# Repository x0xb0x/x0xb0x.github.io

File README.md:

# x0xb0x.github.io
Please view on [http://x0xb0x.github.io](http://x0xb0x.github.io)

All info licensed CC-BY, all software licenced MIT.

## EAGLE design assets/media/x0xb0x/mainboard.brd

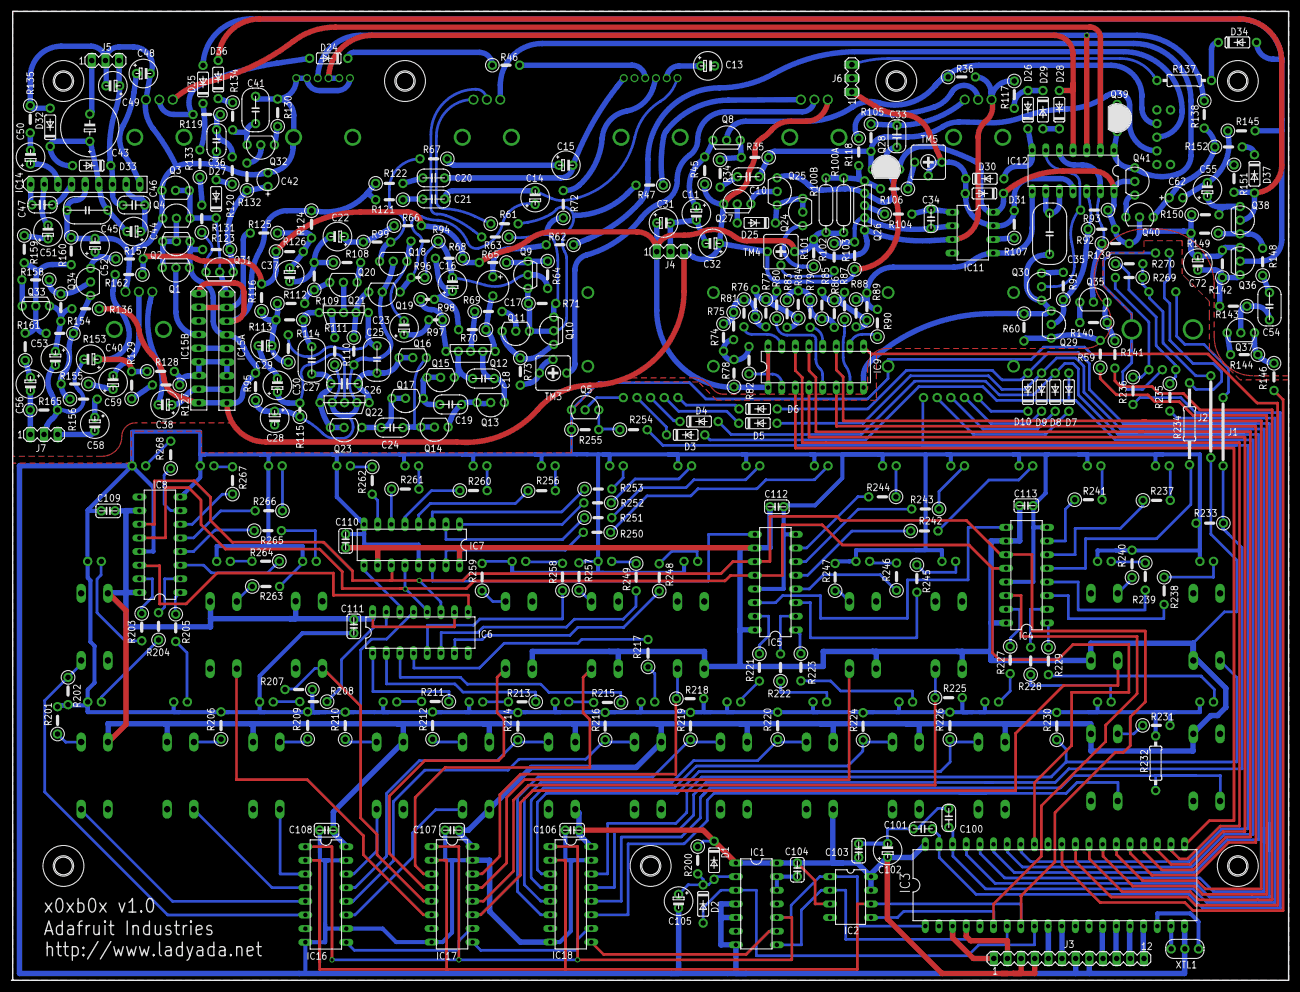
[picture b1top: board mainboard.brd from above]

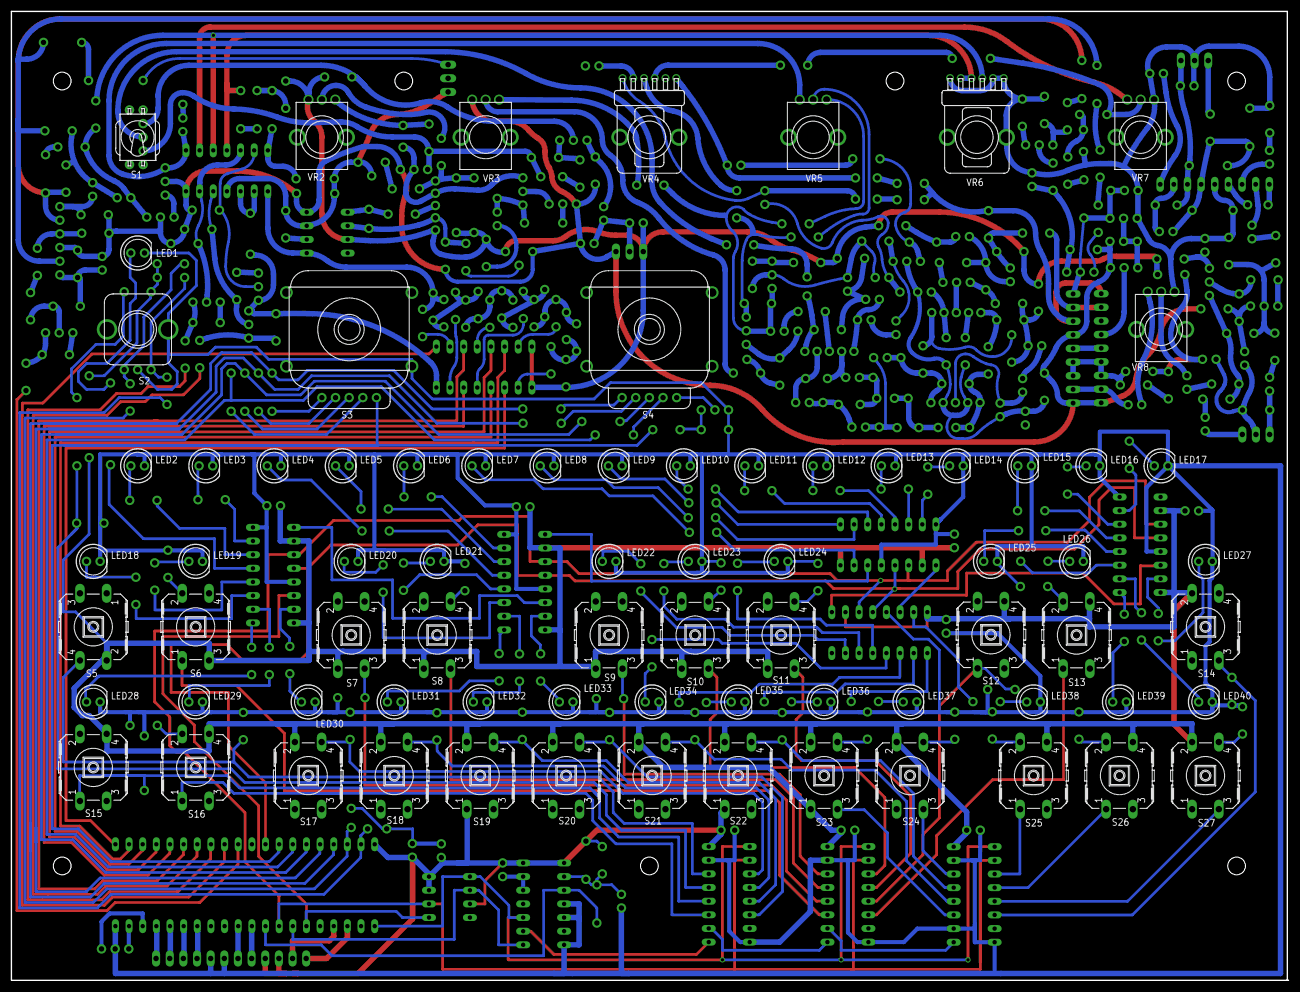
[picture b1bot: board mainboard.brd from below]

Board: 2 copper layers, 237.5 x 180.3 mm, 417 parts (74 on the bottom side), 324 nets.

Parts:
C10, C20, C21, C33, C46: .01; C050-024X044
C11, C13, C14, C15, C22, C23, C29, C38, C56, C58, C59, C105: 1/50; E5-6
C16, C30, C31, C32, C37, C40, C50, C52, C72: 10/16; E5-6
C17: 1/50; E3,5-8
C18: .018; C050-025X075
C19, C24, C36: .033; C050-025X075
C25, C27, C41: .1; C050-030X075
C26: .033; C075-032X103
C28, C44, C53, C55: 47/16; E5-6
C34, C100, C101: .001; C050-035X075
C35: .22; C050-045X075
C42, C62: 1/35; E2,5-7
C43: 1000/6.3; E5-5
C45: .068; C050-050X075
C47: .0068; C050-075X075
C48, C49: 100/6.3; E5-6
C51: 2.2/50; E5-6
C54: .047; C050-055X075
C102: 100/10; E5-6
C103, C104, C106, C107, C108, C109, C110, C111, C112, C113: .1; C050H075X075
D1, D2, D3, D4, D5, D6, D7, D8, D9, D10, D24, D25, D26, D27, D28, D29, D30, D31, D32, D33, D34, D35, D36, D37: 1N4148; DO35-10
IC1: 74126N; DIL14
IC2: AT25P; DIL08
IC3: MEGA162P; DIL40
IC4, IC5, IC6, IC7, IC8: 74HC595N; DIL16
IC9: 4174P; DIL16
IC11: DIL08
IC12: 4066N; DIL14
IC14: LA44140; SIP9
IC15A: SIP9
IC15B: BA6110; SIP9
IC16, IC17, IC18: 74HC165N; DIL16
J1: J12MM; 12
J2: J15MM; 15
J3: MA12-1
J4, J5, J6, J7: MA03-1
LED1, LED2, LED3, LED4, LED5, LED6, LED7, LED8, LED9, LED10, LED11, LED12, LED13, LED14, LED15, LED16, LED17, LED18, LED19, LED20, LED21, LED22, LED23, LED24, LED25, LED26, LED27, LED28, LED29, LED30, LED31, LED32, LED33, LED34, LED35, LED36, LED37, LED38, LED39, LED40: LED5MM
Q1, Q2, Q8, Q9, Q10, Q27, Q31, Q33, Q36, Q38: 2SA733P; TO92
Q3, Q4, Q5, Q11, Q13, Q14, Q15, Q16, Q18, Q20, Q24, Q25, Q29, Q30, Q32, Q34, Q35, Q37, Q40, Q41: 2SC536F
Q12, Q21, Q26: 2SC1583; SSIP5
Q17, Q23: 2SC536F; 2SC536_UNEVEN
Q19: 2SC536FUNEVEN; 2SC536_UNEVEN
Q22: 2SC2291; SSIP5
Q28, Q39: 2SK30
R34, R36, R47, R61, R64, R65, R94, R101, R105, R109, R112, R116, R142, R143, R144, R145, R148, R149, R201, R202, R203, R204, R205, R206, R207, R208, R209, R210, R211, R212, R213, R214, R215, R216, R217, R218, R219, R220, R221, R222, R223, R224, R225, R226, R227, R228, R229, R230, R231, R233, R237, R238, R239, R240, R241, R242, R243, R244, R245, R246, R247, R248, R249, R250, R251, R252, R253, R254, R255, R256, R257, R258, R259, R260, R261, R262, R263, R264, R265, R266, R267, R268, R269, R270: 10K; 0207/5V
R35, R59, R66, R72, R73, R92, R93, R99, R102, R113, R114, R118, R122, R139, R140, R141, R154, R156, R165: 100K; 0207/5V
R45, R60, R110, R111, R117, R129, R134, R146, R151: 22K; 0207/5V
R46, R119, R127, R155: 47K; 0207/5V
R62, R63, R121, R128, R131: 220K; 0207/5V
R67, R68, R69, R70, R71, R104, R107, R108, R124, R125, R126, R133, R162: 2.2K; 0207/5V
R74, R75, R76, R77, R78, R79, R80, R81, R82, R83, R84, R85, R86, R87, R88, R89: 200K; 0207/5V
R90: 200k; 0207/5V
R91, R200: 1M; 0207/5V
R95, R130, R132, R136, R152: 100; 0207/5V
R96, R97, R115: 10K; 0207/2V
R98: 2.2K; 0207/2V
R100A, R100B: THERMISTOR-7,5; R-7,5
R103, R235, R236: 220k; 0207/5V
R106: 27K; 0207/5V
R120: 22k; 0207/5V
R123: 1.5M; 0207/5V
R135: 4.7k; 0207/5V
R137: 1K; 0207/10
R138: 68K; 0207/5V
R150: 22; 0207/5V
R153: 100k; 0207/5V
R157, R158, R160: 10k; 0207/5V
R159: 33K; 0207/5V
R161: 1K; 0207/5V
R232: 10K; 0207/10
R234: 10K; 0207/15
S1: SWITCH_GND; NKKTOGGLE
S2: PEC11-S
S3, S4: GH3074
S5, S6, S7, S8, S9, S10, S11, S12, S13, S14, S15, S16, S17, S18, S19, S20, S21, S22, S23, S24, S25, S26, S27: B3F-40XX
TM3: 500K(B); 306
TM4: 50K(B); 306
TM5: 5K(B); 306
U$2, U$23, U$24, U$25, U$27, U$28, U$29: 1,3
VR2, VR7: 50K(B); EVU
VR3, VR5, VR8: 50K(A); EVU
VR4: 50K(B); ALPHADUAL
VR6: 1M(A); ALPHADUAL
XTL1: 2SC2021R; 2SC2021

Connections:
+5.333V: C31.+, IC9.1, IC9.16, IC11.3, J4.1, Q26.1, R36.2, R65.2, R66.2, R68.1, R78.1, R100A.2, R100B.1, R101.2, R116.2, R117.1, R126.1, R157.2, R162.1, TM4.3, VR2.3
+5V: C102.+, C103.1, C104.2, C106.2, C107.2, C108.2, C109.2, C110.2, C111.2, C112.2, C113.2, D1.C, IC1.1, IC1.14, IC2.3, IC2.7, IC2.8, IC3.40, IC4.10, IC4.16, IC5.10, IC5.16, IC6.10, IC6.16, IC7.10, IC7.16, IC8.10, IC8.16, IC16.16, IC17.16, IC18.16, J2.2, J3.3, J3.4, R200.1, S5.2, S6.3, S7.1, S8.1, S9.1, S10.1, S11.1, S12.4, S13.4, S14.2, S15.4, S16.4, S17.2, S18.2, S19.1, S19.2, S20.2, S21.2, S22.1, S22.2, S23.1, S23.2, S24.2, S25.4, S26.4, S27.2
+6V: C46.1, C49.+, D33.C, IC14.7, J5.3
+12V: C32.+, C72.+, D31.C, IC11.8, IC12.14, IC15A.4, IC15A.9, IC15B.9, J4.3, Q1.3, Q2.3, Q27.3, Q28.1, Q36.3, Q40.2, Q41.2, R45.1, R92.2, R93.1, R95.2, R103.1, R123.2, R136.1, R139.2, R142.2, R149.2, R150.1, TM4.1, VR3.3
ACCENT: IC3.28, R141.2
C48: C48.+, IC14.9
DINSYNC1: IC3.17, J3.12
DINSYNC2: IC3.16, J3.11
DINSYNC3: IC3.15, J3.10
DINSYNC4: IC3.14, J3.9
GATE: IC3.30, R146.2
GND: C11.-, C13.-, C16.-, C22.-, C28.-, C29.-, C30.-, C31.-, C32.-, C33.2, C35.2, C36.2, C37.-, C40.-, C41.2, C42.-, C45.2, C48.-, C49.-, C52.-, C53.-, C55.-, C62.-, C100.1, C101.1, C102.-, C103.2, C104.1, C105.-, C106.1, C107.1, C108.1, C109.1, C110.1, C111.1, C112.1, C113.1, D26.C, D30.A, D32.A, IC1.4, IC1.5, IC1.7, IC1.12, IC1.13, IC2.4, IC3.20, IC4.8, IC4.13, IC5.8, IC5.13, IC6.8, IC6.13, IC7.8, IC7.13, IC8.8, IC8.13, IC9.8, IC11.4, IC12.7, IC14.5, IC15A.5, IC15B.3, IC15B.5, IC16.8, IC16.10, IC16.15, IC17.8, IC17.15, IC18.8, IC18.15, J3.7, J3.8, J4.2, J5.2, J6.2, J7.2, LED1.K, LED2.K, LED3.K, LED4.K, LED5.K, LED6.K, LED7.K, LED8.K, LED9.K, LED10.K, LED11.K, LED12.K, LED13.K, LED14.K, LED15.K, LED16.K, LED17.K, LED18.K, LED19.K, LED20.K, LED21.K, LED22.K, LED23.K, LED24.K, LED25.K, LED26.K, LED27.K, LED28.K, LED29.K, LED30.K, LED31.K, LED32.K, LED33.K, LED34.K, LED35.K, LED36.K, LED37.K, LED38.K, LED39.K, LED40.K, Q3.3, Q4.3, Q5.3, Q9.2, Q29.3, Q30.3, Q35.3, Q37.3, Q39.2, Q39.3, R60.1, R64.2, R94.1, R96.1, R105.1, R108.1, R109.2, R130.2, R135.1, R140.2, R144.2, R145.1, R151.1, R160.1, R165.2, R201.2, R202.2, R206.2, R207.1, R209.2, R210.2, R212.2, R214.2, R216.2, R218.2, R219.2, R220.2, R224.2, R225.2, R226.2, R230.2, R231.2, R232.2, R233.2, R240.2, R247.2, R255.1, R257.2, R259.2, R263.2, S1.M1, S1.M2, S1.M3, S1.M4, S2.C, S2.P$1, S2.P$2, S3.MT1, S3.MT2, S3.MT3, S3.MT4, S4.MT1, S4.MT2, S4.MT3, S4.MT4, VR2.1, VR2.M1, VR2.M2, VR3.M1, VR3.M2, VR4.1A, VR4.M1, VR4.M2, VR5.M1, VR5.M2, VR6.1A, VR6.2A, VR6.3A, VR6.M1, VR6.M2, VR7.1, VR7.M1, VR7.M2, VR8.1, VR8.M1, VR8.M2, XTL1.2
LED_LATCH: IC3.32, IC4.12, IC5.12, IC6.12, IC7.12, IC8.12
MIDI_IN: IC3.10, J3.5
MIDI_OUT: IC3.11, J3.6
unnamed: C51.-, IC14.2
unnamed: C51.+, R159.1
unnamed: C50.+, IC14.3
unnamed: C50.-, R135.2
unnamed: Q34.3, R153.1, R155.2, R156.1
unnamed: C56.+, R161.1
unnamed: C56.-, J7.1, R165.1
unnamed: C47.1, IC14.4
unnamed: C47.2, IC14.1
unnamed: C43.-, J5.1
unnamed: C43.+, C44.-, C45.1, D32.C, D33.A, IC14.6
unnamed: Q33.2, R153.2, R159.2, R160.2, R161.2
unnamed: C44.+, C46.2, IC14.8
unnamed: Q34.2, R154.1, R158.1
unnamed: Q33.1, R158.2
unnamed: C53.+, Q33.3, R136.2, R154.2
unnamed: C52.+, Q34.1, R157.1
unnamed: C59.+, R155.1
unnamed: C58.+, R156.2
unnamed: C58.-, J7.3
unnamed: C20.1, R122.2
unnamed: C37.+, R124.2, R125.1, R126.2
unnamed: IC7.1, R252.2
unnamed: IC15A.2, IC15B.2, R125.2
unnamed: C21.1, R121.1
unnamed: C15.-, C20.2, VR4.2A
unnamed: C14.-, C21.2, VR4.3A
unnamed: IC15A.6, IC15A.7, IC15B.6, IC15B.7, R127.1, R128.2
unnamed: IC15B.4, Q1.2
unnamed: R127.2, R129.1
unnamed: C40.+, R128.1, R129.2, R162.2
unnamed: C38.-, VR8.3
unnamed: D27.A, R120.1
unnamed: C36.1, R119.1, R120.2
unnamed: D24.A, R119.2, VR7.2
unnamed: C55.+, Q38.3, R150.2
unnamed: C72.-, Q36.1, R142.1, R143.2
unnamed: D34.A, D35.A, Q36.2, R145.2
unnamed: Q38.1, R148.2, R149.1
unnamed: D37.C, R152.2
unnamed: C54.1, R148.1
unnamed: C54.2, Q37.2, R143.1
unnamed: Q37.1, R144.1, R146.1
unnamed: D36.A, D37.A, Q38.2, R151.2
unnamed: C62.+, Q40.1, R138.2, R152.1
unnamed: Q40.3, Q41.1
unnamed: C38.+, IC15A.8, IC15B.8
unnamed: R61.1, VR5.1
unnamed: D26.A, D29.C, R117.2
unnamed: D28.C, D29.A
unnamed: D28.A, IC12.4, VR6.2B, VR6.3B
unnamed: IC12.1, Q39.1, Q41.3, VR5.3
unnamed: Q35.1, R140.1, R141.1
unnamed: Q32.3, R130.1
unnamed: IC12.5, IC12.13, Q35.2, R139.1
unnamed: D34.C, R137.1
unnamed: Q5.1, R254.1, R255.2
unnamed: Q12.5, R97.1, R98.1
unnamed: D35.C, R133.2
unnamed: D36.C, R134.1
unnamed: C41.1, Q32.1, R134.2
unnamed: Q32.2, R132.2
unnamed: C42.+, Q31.1, R123.1, R132.1
unnamed: D27.C, IC15A.1, Q3.1, Q3.2, Q4.1, Q31.2
unnamed: Q31.3, R131.1
unnamed: R131.2, R133.1
unnamed: IC9.10, R90.1
unnamed: R236.1, R269.2, S2.B
unnamed: IC4.7, R241.1
unnamed: C35.1, IC12.9, IC12.10
unnamed: IC12.6, Q30.2, R93.2
unnamed: Q30.1, R91.2
unnamed: IC11.6, R107.1
unnamed: R85.2, R86.1, R87.2, R88.2, R89.1
unnamed: IC1.9, IC18.9
unnamed: IC12.12, Q29.2, R91.1, R92.1
unnamed: R79.1, R83.1, R84.2, R85.1, R86.2
unnamed: C105.+, D1.A, D2.C, IC1.2, R200.2
unnamed: IC9.15, R81.2
unnamed: IC9.2, R82.1
unnamed: IC9.12, R79.2
unnamed: Q29.1, R59.2, R60.2
unnamed: C34.1, IC11.1, R104.2
unnamed: C34.2, IC11.2, Q26.2, R102.1, R103.2
unnamed: Q26.5, R100A.1, R100B.2, R106.2, R118.2
unnamed: IC4.6, R237.1
unnamed: Q26.3, R104.1
unnamed: R118.1, VR2.2
unnamed: D25.A, Q27.2
unnamed: D25.C, Q24.1, Q24.2, Q25.1
unnamed: Q24.3, R101.1
unnamed: Q25.2, Q27.1
unnamed: IC17.5, R207.2, S12.1
unnamed: C10.1, Q28.3, R35.1, R105.2, S1.1
unnamed: Q8.1, R34.1, R35.2
unnamed: C10.2, R34.2
unnamed: IC11.5, IC12.8, R88.1, R89.2, R90.2
unnamed: C33.1, Q25.3, Q26.4, Q28.2
unnamed: R102.2, TM4.2
unnamed: C30.+, Q22.3, R115.2
unnamed: C24.1, Q14.1, Q14.2, Q16.3
unnamed: C19.1, Q13.1, Q13.2, Q14.3
unnamed: C18.2, Q12.2, Q13.3
unnamed: C24.2, Q17.1, Q17.2, Q23.3
unnamed: C26.2, C27.1, Q22.5, Q23.1, Q23.2
unnamed: C18.1, Q12.4, Q15.3
unnamed: C28.+, Q18.2, Q19.2, Q22.2, Q22.4, R95.1, R110.2, R111.1, R115.1
unnamed: C17.+, R62.2
unnamed: C17.-, Q12.1, R70.1
unnamed: C16.+, R68.2, R70.2, R98.2
unnamed: R62.1, S1.2
unnamed: Q12.3, R69.1
unnamed: C23.+, R97.2
unnamed: LED6.A, R244.1
unnamed: C23.-, Q18.3, R94.2
unnamed: Q18.1, R67.2, R99.2
unnamed: C22.+, R66.1, R99.1
unnamed: C15.+, R67.1
unnamed: Q10.1, R63.1, R71.2, R72.1
unnamed: Q20.1, R109.1, R112.2
unnamed: Q20.3, R108.2
unnamed: LED7.A, R250.1
unnamed: C25.2, Q21.1, R114.2
unnamed: Q20.2, Q21.3
unnamed: Q19.1, Q21.2, R110.1
unnamed: C27.2, Q21.5, R113.1
unnamed: R47.1, VR3.1
unnamed: C25.1, C26.1, Q16.1, Q16.2, Q22.1
unnamed: C14.+, Q19.3, R96.2
unnamed: Q11.2, R69.2
unnamed: Q10.3, Q11.1, R73.1
unnamed: Q21.4, R111.2
unnamed: Q9.1, R64.1, R65.1
unnamed: IC12.2, VR7.3
unnamed: R73.2, TM3.2, TM3.3
unnamed: R72.2, VR4.2B
unnamed: R63.2, VR5.2
unnamed: TM3.1, VR3.2
unnamed: R76.2, R77.1, R80.2, R83.2, R84.1
unnamed: IC12.3, R138.1, VR6.1B
unnamed: R106.1, TM5.1
unnamed: C59.-, VR8.2
unnamed: D24.C, R46.1
unnamed: R46.2, VR4.1B
unnamed: C13.+, VR4.3B
unnamed: R257.1, S10.4
unnamed: IC17.14, R218.1, S9.3
unnamed: IC17.13, S8.3
unnamed: IC17.12, R225.1, S7.3
unnamed: R259.1, S11.4
unnamed: IC18.14, R230.1, S5.4
unnamed: D3.C, S4.P$1
unnamed: IC18.12, R232.1, S15.1
unnamed: R206.1, S26.2
unnamed: IC16.5, S27.3
unnamed: IC17.9, IC18.10
unnamed: IC18.4, R224.1, S18.4
unnamed: IC17.4, S11.3
unnamed: D4.C, S4.P$2
unnamed: R209.1, S25.2
unnamed: IC4.5, R234.1
unnamed: IC5.9, IC7.14
unnamed: IC5.6, R243.2
unnamed: IC5.7, R244.2
unnamed: IC5.5, R242.1
unnamed: IC7.15, R250.2
unnamed: IC7.2, R251.1
unnamed: LED1.A, R234.2
unnamed: LED2.A, R237.2
unnamed: IC7.3, R253.1
unnamed: IC7.4, R256.1
unnamed: LED14.A, R262.1
unnamed: IC8.3, R264.1
unnamed: IC8.6, R267.1
unnamed: IC8.7, R268.1
unnamed: IC8.5, R266.2
unnamed: IC5.1, R223.1
unnamed: IC8.4, R265.1
unnamed: IC5.2, R222.2
unnamed: IC5.15, R221.1
unnamed: IC5.4, R246.1
unnamed: IC5.3, R245.2
unnamed: IC4.3, R238.2
unnamed: IC4.4, R239.2
unnamed: IC4.1, R229.1
unnamed: IC7.6, R261.1
unnamed: IC7.7, R262.2
unnamed: IC7.5, R260.1
unnamed: IC4.2, R228.2
unnamed: IC4.15, R227.1
unnamed: IC8.15, R203.1
unnamed: IC8.1, R205.1
unnamed: IC8.2, R204.2
unnamed: IC6.15, R208.1
unnamed: IC6.1, R211.1
unnamed: IC6.2, R213.1
unnamed: IC6.3, R215.1
unnamed: IC6.4, R217.2
unnamed: IC6.7, R248.1
unnamed: IC6.6, R249.2
unnamed: IC6.5, R258.1
unnamed: IC16.9, IC17.10
unnamed: IC16.13, R214.1, S22.4
unnamed: R210.1, S24.4
unnamed: IC16.11, S23.3
unnamed: IC16.4, S26.1
unnamed: IC18.6, R219.1, S20.4
unnamed: IC16.12, R216.1, S21.4
unnamed: R240.1, S6.2
unnamed: IC16.14, S24.3
unnamed: IC9.7, R87.1
unnamed: R201.1, S27.4
unnamed: R235.1, R270.1, S2.A
unnamed: R212.1, S23.4
unnamed: IC9.5, R80.1
unnamed: R74.2, R75.2, R78.2, R82.2
unnamed: LED9.A, R252.1
unnamed: LED10.A, R253.2
unnamed: LED11.A, R256.2
unnamed: LED12.A, R260.2
unnamed: IC18.5, R220.1, S19.4
unnamed: R74.1, R75.1, R76.1, R77.2, R81.1
unnamed: R231.1, S16.2
unnamed: IC16.6, R202.1, S14.3
unnamed: R263.1, S13.2
unnamed: Q5.2, S4.C
unnamed: IC17.6, S13.1
unnamed: IC18.3, R226.1, S17.4
unnamed: IC17.3, S10.3
unnamed: LED16.A, R267.2
unnamed: IC17.11, S6.1
unnamed: IC18.11, S16.1
unnamed: IC16.3, S25.1
unnamed: R247.1, S8.4
unnamed: LED3.A, R241.2
unnamed: LED4.A, R242.2
unnamed: LED5.A, R243.1
unnamed: LED15.A, R266.1
unnamed: LED8.A, R251.2
unnamed: LED13.A, R261.2
unnamed: IC4.9, IC5.14
unnamed: IC6.14, IC7.9
unnamed: IC6.9, IC8.14
unnamed: LED17.A, R268.2
unnamed: LED18.A, R238.1
unnamed: LED19.A, R239.1
unnamed: LED20.A, R245.1
unnamed: LED21.A, R246.2
unnamed: LED22.A, R248.2
unnamed: LED23.A, R249.1
unnamed: LED24.A, R258.2
unnamed: LED25.A, R265.2
unnamed: LED26.A, R264.2
unnamed: LED27.A, R203.2
unnamed: LED28.A, R229.2
unnamed: LED29.A, R228.1
unnamed: LED30.A, R227.2
unnamed: LED31.A, R223.2
unnamed: LED32.A, R222.1
unnamed: LED33.A, R221.2
unnamed: LED34.A, R217.1
unnamed: LED35.A, R215.2
unnamed: LED36.A, R213.2
unnamed: LED37.A, R211.2
unnamed: LED38.A, R208.2
unnamed: LED39.A, R205.2
unnamed: LED40.A, R204.1
unnamed: D2.A, IC1.3, IC3.9
unnamed: D5.C, S4.P$4
unnamed: D6.C, S4.P$8
unnamed: D7.C, S3.P$1
unnamed: D8.C, S3.P$2
unnamed: D9.C, S3.P$4
unnamed: D10.C, S3.P$8
unnamed: C11.+, Q8.3, R45.2
unnamed: Q8.2, R36.1, S1.3
unnamed: J1.1, S2.SW1
unnamed: J2.1, R269.1, R270.2, S2.SW2
unnamed: IC3.18, XTL1.3
unnamed: Q9.3, Q10.2, Q11.3, R47.2, R61.2, R71.1
unnamed: C29.+, R112.1, R113.2, R114.1, R116.1
unnamed: Q1.1, Q2.1, Q2.2, Q4.2
unnamed: J6.3, R137.2
unnamed: IC15A.3, IC15B.1, R121.2, R122.1, R124.1
unnamed: D30.C, D31.A, IC11.7, IC12.11, J6.1, R107.2, TM5.2, TM5.3
NOTE0: IC3.21, IC9.3
NOTE1: IC3.22, IC9.14
NOTE2: IC3.23, IC9.4
NOTE3: IC3.24, IC9.13
NOTE4: IC3.25, IC9.6
NOTE5: IC3.26, IC9.11
NOTE_LATCH: IC3.29, IC9.9
Q17: C19.2, Q15.1, Q15.2, Q17.3
ROTARY1: D3.A, D7.A, IC3.34
ROTARY2: D4.A, D8.A, IC3.35
ROTARY4: D5.A, D9.A, IC3.36
ROTARY8: D6.A, D10.A, IC3.37
ROTARYCOM3: IC3.33, R254.2, S3.C
SLIDE: IC3.27, R59.1
SPI_CLK: IC2.6, IC3.8, IC4.11, IC5.11, IC6.11, IC7.11, IC8.11, IC16.2, IC17.2, IC18.2
SPI_IN: IC2.5, IC3.6, IC4.14
SPI_OUT: IC1.8, IC2.2, IC3.7
SWITCH_LATCH: IC1.10, IC2.1, IC3.1, IC16.1, IC17.1, IC18.1
TEMPO_SW: IC18.13, J1.2, R233.1
TEMPO_SW_A: C100.2, IC3.38, R235.2
TEMPO_SW_B: C101.2, IC3.39, R236.2
USBRX: IC3.3, J3.1
USB_TX: IC3.4, J3.2
XTL1: IC3.19, XTL1.1

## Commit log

2015-11-20 Replace master branch with page content via GitHub
2015-11-29 Scrape from ladyada.net/make/x0xb0x , purge menus, some whitespace cleaning
2015-11-29 Move scripts, images, fonts and other files to assets dir
2015-11-30 Relocate assets
2015-11-30 Simplify layout, remove redundant files
2015-11-30 Move header to single instance, remove redundant files
2015-11-30 Move assets
2015-11-30 Layout for make section
2016-02-22 Create CNAME
2016-02-27 Remove dead links
2016-02-27 Line endings settings
2016-02-27 Remove redundant example content
2016-02-27 gitignore
2016-02-27 Add dropped forwarding instruction
2016-02-27 Correction on general page subtitle, re-insert dropped referral line
2016-02-27 Line endings
2016-02-28 Provide Github fork ribbon
2016-02-28 Include better licensing info
2016-03-01 Updated broken link to forums
2016-04-17 Add ioboard and mainboard schematics for Eagle, PDF and DXF
2016-04-27 D3.js stub for interactive web schematics, add run script for convenience, move some files around
2019-09-25 Add brd and sch files and adjust download page
